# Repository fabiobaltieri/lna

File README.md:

LNA
===

http://fabiobaltieri.com/2014/06/22/lna/

This project is an LNA board based on the PSA4-5043+.

License
-------

This work is licensed under a Creative Commons Attribution-ShareAlike 3.0
License.

Contents
--------

    README this file
    lna/   source directory for the hardware design

Hardware
--------

All hardware files (schematic, layout and libraries) are in CadSoft Eagle
format.

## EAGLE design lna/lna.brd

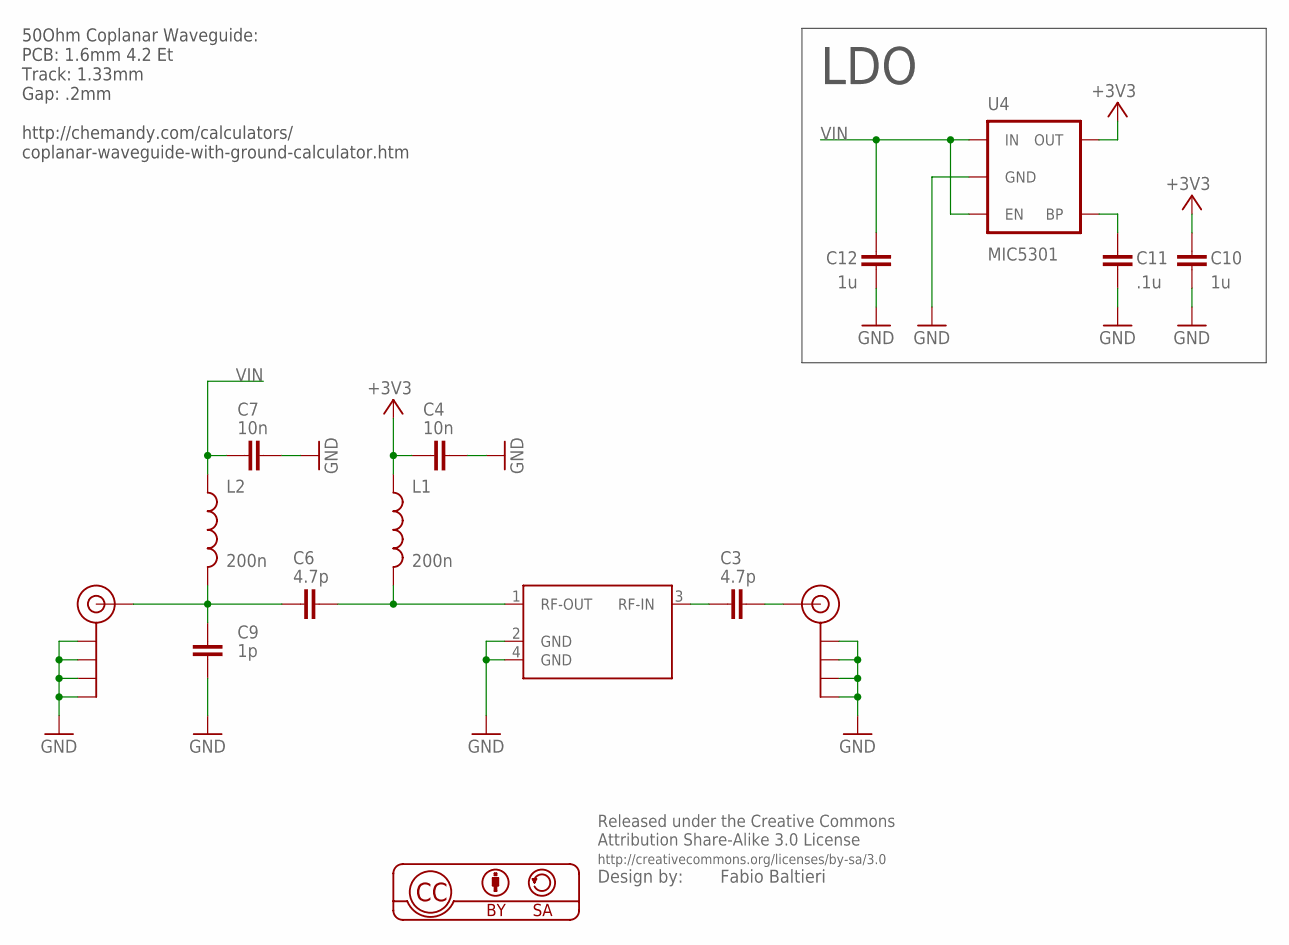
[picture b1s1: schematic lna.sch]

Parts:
C3, C6: 4.7p; C0603
C4, C7: 10n; C0603
C9: 1p; C0603
C10, C12: 1u; C0603
C11: .1u; C0603
J$1, J$2: SMA_EDGE; SMA-EDGE
L1, L2: 200n; 0603
U1: PSA4-5043; SOT343R
U4: MIC5301; SOT23-5

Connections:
+3V3: C4.1, C10.1, L1.1, U4.5 (OUT)
GND: C4.2, C7.2, C9.2, C10.2, C11.2, C12.2, J$1.GND@0 (GND), J$1.GND@1 (GND), J$1.GND@2 (GND), J$1.GND@3 (GND), J$2.GND@0 (GND), J$2.GND@1 (GND), J$2.GND@2 (GND), J$2.GND@3 (GND), U1.2 (GND), U1.4 (GND), U4.2 (GND)
unnamed: C3.2, J$2.SIG (SIGNAL)
unnamed: C3.1, U1.3 (RF-IN)
unnamed: C6.2, L1.2, U1.1 (RF-OUT)
unnamed: C11.1, U4.4 (BP)
unnamed: C6.1, C9.1, J$1.SIG (SIGNAL), L2.2
VIN: C7.1, C12.1, L2.1, U4.1 (IN), U4.3 (EN)

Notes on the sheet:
LDO
50Ohm Coplanar Waveguide: PCB: 1.6mm 4.2 Et Track: 1.33mm Gap: .2mm http://chemandy.com/calculators/ coplanar-waveguide-with-ground-calculator.htm

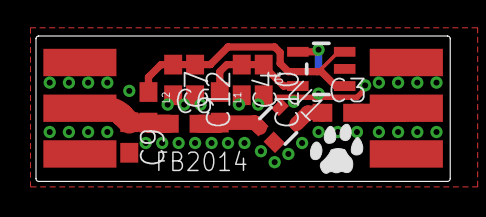
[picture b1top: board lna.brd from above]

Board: 2 copper layers, 23.0 x 8.1 mm, 15 parts (1 on the bottom side), 8 nets.

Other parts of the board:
U$1: CAT-L

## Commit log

2014-03-23 r1 (for real)
2014-06-15 lna: add pdf schematics
2014-06-15 add README file
2014-06-23 README.md: fix wp link
2014-06-27 README: fix description alignment
2014-07-17 hw: correct lna part number

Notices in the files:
parts and their libraries:
SparkFun-Connectors: Licensing: CC v3.0 Share-Alike You are welcome to use this library for commercial purposes.
balto: Released under the Creative Commons
balto: http://creativecommons.org/licenses/by-sa/3.0
